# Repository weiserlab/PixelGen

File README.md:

# PixelGen: Rethinking Embedded Cameras for Mixed-Reality

## Overview
Mixed-reality headsets offer new ways to perceive our environment. They employ visible spectrum cameras to capture and display the environment on screens in front of the user's eyes. However, these cameras lead to limitations. Firstly, they capture only a partial view of the environment. They are positioned to capture whatever is in front of the user, thus creating blind spots during complete immersion and failing to detect events outside the restricted field of view. Secondly, they capture only visible light fields, ignoring other fields like acoustics and radio that are also present in the environment. Finally, these power-hungry cameras rapidly deplete the mixed-reality headset's battery. We introduce PixelGen to rethink embedded cameras for mixed-reality headsets. PixelGen proposes to decouple cameras from the mixed-reality headset and balance resolution and fidelity to minimize the power consumption. It employs low-resolution, monochrome image sensors and environmental sensors to capture the surroundings around the headset. This approach reduces the system's communication bandwidth and power consumption. A transformer-based language and image model process this information to overcome resolution trade-offs, thus generating a higher-resolution representation of the environment. 

## Demonstration
View what **`PixelGen`** can do! Here are a stream of images generated from PixelGen- 
http://bit.ly/generated_video

## Publications
1. [**ImmerCom'24**](https://dl.acm.org/doi/10.1145/3636534.3696216) - *PixelGen: Rethinking Embedded Cameras for Mixed-Reality*
   > The 2nd ACM Workshop on Mobile Immersive Computing, Networking, and Systems (**ImmerCom**) was held in conjunction with **ACM MobiCom 2024**
   ```
   @inproceedings{10.1145/3636534.3696216,
      author = {Li, Kunjun and Gulati, Manoj and Shah, Dhairya and Waskito, Steven and Chakrabarty, Shantanu and Varshney, Ambuj},
      title = {PixelGen: Rethinking Embedded Cameras for Mixed-Reality},
      year = {2024},
      isbn = {9798400704895},
      publisher = {Association for Computing Machinery},
      address = {New York, NY, USA},
      url = {https://doi.org/10.1145/3636534.3696216},
      doi = {10.1145/3636534.3696216},
      abstract = {Mixed-reality headsets offer new ways to perceive our environment. They employ visible spectrum cameras to capture and display the environment on screens in front of the user's eyes. However, these cameras lead to limitations. Firstly, they capture only a partial view of the environment. They are positioned to capture whatever is in front of the user, thus creating blind spots during complete immersion and failing to detect events outside the restricted field of view. Secondly, they capture only visible light fields, ignoring other fields like acoustics and radio that are also present in the environment. Finally, these power-hungry cameras rapidly deplete the mixed-reality headset's battery. We introduce PixelGen to rethink embedded cameras for mixed-reality headsets. PixelGen proposes to decouple cameras from the mixed-reality headset and balance resolution and fidelity to minimize the power consumption. It employs low-resolution, monochrome image sensors and environmental sensors to capture the surroundings around the headset. This approach reduces the system's communication bandwidth and power consumption. A transformer-based language and image model process this information to overcome resolution trade-offs, thus generating a higher-resolution representation of the environment. We present initial experiments that show PixelGen's viability.},
      booktitle = {Proceedings of the 30th Annual International Conference on Mobile Computing and Networking},
      pages = {2128–2135},
      numpages = {8},
      keywords = {embedded systems, networking, large language models},
      location = {Washington D.C., DC, USA},
      series = {ACM MobiCom '24}
   }
   ```
3. [**IPSN'24 Demo**](https://ieeexplore.ieee.org/document/10577362) - *PixelGen: Rethinking Embedded Camera Systems for Mixed-Reality*
   
   > PixelGen wins [*Best Demonstration Runner-Up* award](https://ipsn.acm.org/2024/awards.html) at IPSN'24.
   ```
   @INPROCEEDINGS{10577362,
      author={Li, Kunjun and Gulati, Manoj and Shah, Dhairya and Waskito, Steven and Chakrabarty, Shantanu and Varshney, Ambuj},
      booktitle={2024 23rd ACM/IEEE International Conference on Information Processing in Sensor Networks (IPSN)}, 
      title={Demo Abstract: PixelGen: Rethinking Embedded Camera Systems for Mixed-Reality}, 
      year={2024},
      volume={},
      number={},
      pages={271-272},
      keywords={Headphones;Visualization;Power demand;Magnetic sensors;Mixed reality;Virtual reality;Sensor phenomena and characterization;Embedded Camera Systems;Mixed Reality;Multimodal AI;Low-power Systems},
      doi={10.1109/IPSN61024.2024.00036}
   }
   ```

4. [**arXiv**](https://arxiv.org/abs/2402.03390) - *PixelGen: Rethinking Embedded Camera Systems*
   ```
   @misc{li2024pixelgenrethinkingembeddedcamera,
      title={PixelGen: Rethinking Embedded Camera Systems}, 
      author={Kunjun Li and Manoj Gulati and Steven Waskito and Dhairya Shah and Shantanu Chakrabarty and Ambuj Varshney},
      year={2024},
      eprint={2402.03390},
      archivePrefix={arXiv},
      primaryClass={eess.IV},
      url={https://arxiv.org/abs/2402.03390}, 
   }
   ```

## Repository Contents
This repository contains everything you need to get started with PixelGen, including scripts, hardware designs, and model compression tools.

### Pipeline
- **`fast_stable_diffusion_AUTOMATIC1111.ipynb`**: This script runs the diffusion model on collected sensor data to generate high-resolution images.
- **`ControlNet`**: This repo gives a quick guide to use controlnet with stable diffusion (either by canny edge detector or oneformer segmentation)
  
### Script
- **`capture.py`**: This script captures a low-res monochrome image using the PixelGen platform.
- **`fusion.py`**: This script captures an image and simultaneously collect sensor data.
  
### Hardware
- **`AmbiqSDK`**: Contains the driver code required to interface with the various sensors and microcontroller on the PixelGen platform.
- **`board`**: Includes the schematics of the hardware components, detailing how the sensors, microcontroller, and transceivers are interconnected. It also provides the Gerber files needed for manufacturing the custom PixelGen board.
  
### Beta
This repo contains pruning.ipynb which can compress stable diffusion 3 transformer with one-shot pruning ([SparseGPT](https://arxiv.org/abs/2301.00774)) and Tiny-SD which is a compressed stable diffusion v1.5 model with [`knowledge distillation`](https://github.com/segmind/distill-sd). Note that the work is still in progress.

## Getting Started
1. **Clone the repository**: 
   ```bash
   git clone https://github.com/weiserlab/PixelGen.git
   cd PixelGen
   ```
## Poster
This shows a high level overview of **PixelGen**.

## Contributing
We welcome contributions from the community. Please fork the repository and create a pull request with your enhancements or bug fixes.

## Team and Contact
PixelGen is developed and maintained by the following researchers from the [WEISER group](https://weiserlab.github.io/ambuj/) from the School of Computing, National University of Singapore (NUS). 
- [Kunjun Li](https://github.com/StargazerX0) 
- [Manoj Gulati](https://github.com/manojgulati)
- [Dhairya Shah](https://github.com/dhairyashah1/)
- [Steven Waskito](https://github.com/stevenantya)
- [Ambuj Varshney](https://github.com/weiserlab/)
  
Feel free to contact us at [`dhairya@u.nus.edu`](mailto:dhairya@u.nus.edu) or [`ambujv@nus.edu.sg`](mailto:ambujv@nus.edu.sg) for any questions or suggestions.

## Funding
This work was supported primarily through a grant from the NUS-NCS center, a startup grant, a MoE Tier 1 Grant, and an unrestricted gift from Google through their Research Scholar Program. All of these grants were administered through the National University of Singapore.

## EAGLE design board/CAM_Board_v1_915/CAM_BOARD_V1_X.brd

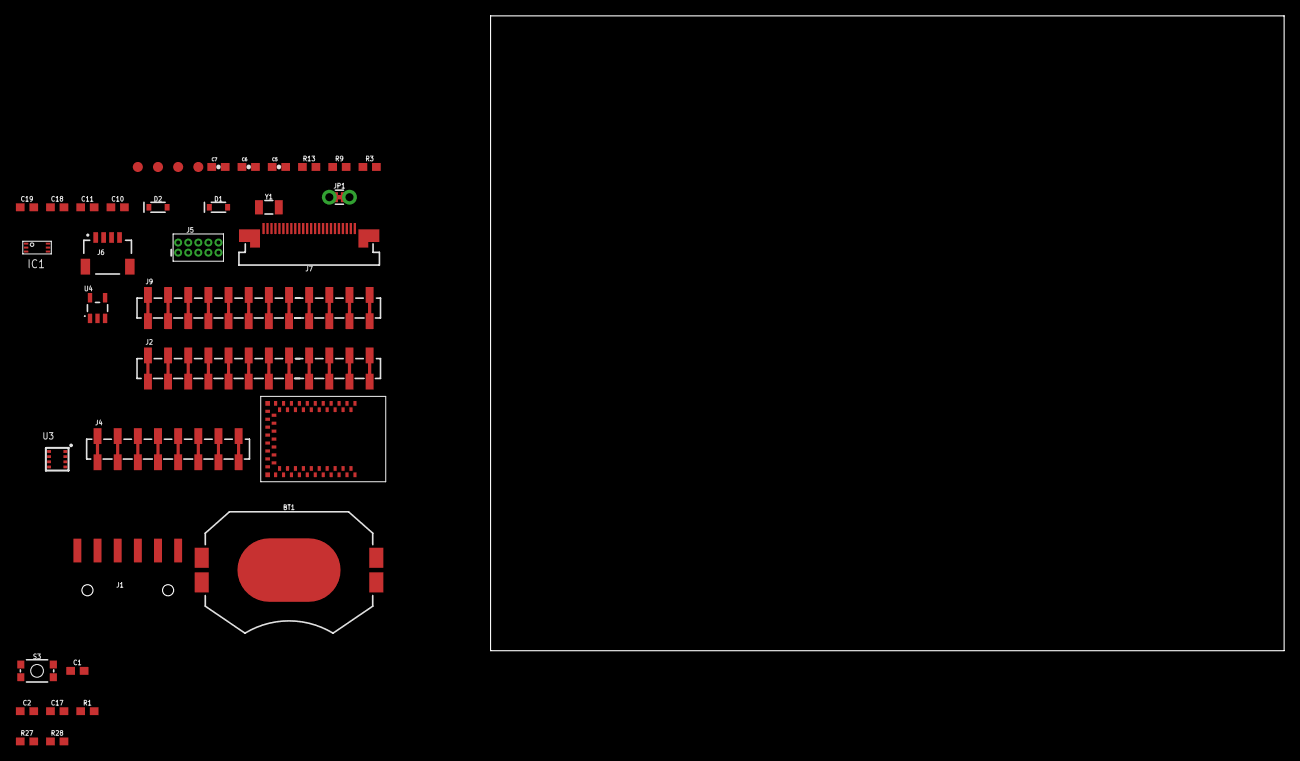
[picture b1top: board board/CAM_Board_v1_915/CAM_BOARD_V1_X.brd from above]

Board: 2 copper layers, 100.0 x 80.0 mm, 37 parts (0 on the bottom side), 63 nets, no tracks yet.

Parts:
BT1: BATTCON_20MM_4LEGS_OVERPASTE_INNER
C1, C2: 0.1uF; 0603
C5, C6, C7: 0.1uF; 0603-CAP
C10, C11: 15pF; 0603
C17: 1nF; 0603
C18, C19: 1.0uF; 0603
D1, D2: 1A/23V/620mV; SOD-323
IC1: BH1750; WSOF-6
J1: 1X06-SMD_RA_MALE
J2, J9: 1X12_SMD_COMBINED
J4: SMD; 1X08_SMD_COMBINED
J5: CORTEX_DEBUG; 2X5-PTH-1.27MM
J6: QWIIC_RIGHT_ANGLE; JST04_1MM_RA
J7: CAMERA-HIMAXBOTTOM-CONTACT; FPC-24-AMPHENOL-SFV24R-1STE1HLF
JP1: JUMPER-COMBO_2_NC_TRACE; COMBO-JUMPER_2_NC_TRACE
R1, R27: 100k; 0603
R3, R9: 1k; 0603@1
R13: 10k; 0603@1
R28: 220k; 0603
S3: RESET; TACTILE_SWITCH_SMD_4.6X2.8MM
TP1, TP2: PAD.03X.05
TP5, TP6: TEST-POINT3X5; PAD.03X.05
U2: ARTEMIS_MODULESMD; ARTEMIS_FP
U3: BME280; BME280_LGA
U4: AP2127K-1.8V; SOT23-5
Y1: 32.768kHz; CRYSTAL-SMD-3.2X1.5MM

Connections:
1.8V: C19.1, J4.7, J4.7@2, J4.8, J4.8@2, J7.10, U4.5
3.3V: J4.5, J4.5@2, J4.6, J4.6@2, J6.2
!DTR: C1.1, C2.1, J1.1, R1.2
!TGT_RST: J5.10, U2.~RST
AMBIQ_!RST: C1.2, C17.1, R27.1, S3.3, S3.4
BOOT: C2.2, R28.2
CAMERA_D0: J7.14, U2.D0
CAMERA_D1: J7.3, U2.D1
CAMERA_D2: J7.9, U2.D2
CAMERA_D3: J7.5, U2.D3
CAMERA_D4: J7.12, U2.~D4
CAMERA_D5: J7.20, U2.~D5
CAMERA_D6: J7.19, U2.~D6
CAMERA_D7: J7.13, U2.D7
CAMERA_HSYNC: J7.16, U2.D17
CAMERA_INT: J7.18, U2.D10
CAMERA_MCLK: J7.8, U2.~D18
CAMERA_PCLK: J7.17, U2.~D19
CAMERA_TRIG: J7.7, U2.D14
CAMERA_VSYNC: J7.6, U2.D15
D13: J9.5, J9.5@2, U2.~AD13
D16: J2.12, J2.12@2, U2.AD16
D23: J9.3, J9.3@2
D24: J9.1, J9.1@2, U2.~D24
D25: J9.11, J9.11@2
D26: J9.10, J9.10@2, U2.~D26
D27: J9.4, J9.4@2
D28: J9.12, J9.12@2, U2.~D28
D29: J9.8, J9.8@2, U2.~AD29
D31: J2.11, J2.11@2, U2.~AD31
D32: J9.7, J9.7@2, U2.~AD32
D33: J9.6, J9.6@2, U2.~AD33/SWO
D34: J9.9, J9.9@2, U2.AD34
D35: J9.2, J9.2@2, U2.~AD35
D36: J2.6, J2.6@2, U2.D36
D37: J2.4, J2.4@2, U2.~D37
D38: J2.5, J2.5@2, U2.D38
D39: J2.1, J2.1@2, U2.~D39
D40: J2.2, J2.2@2, U2.D40
D41: J2.10, J2.10@2, U2.D41
D42: J2.7, J2.7@2, U2.~D42
D43: J2.8, J2.8@2, U2.~D43
D44: J2.3, J2.3@2, U2.~D44
D45: J2.9, J2.9@2, U2.~D45
FTDI_VCC: D2.A, J1.4
GND: BT1.2, C5.2, C6.2, C7.2, C10.1, C11.1, C17.2, C18.2, C19.2, IC1.3, J1.6, J4.1, J4.1@2, J4.2, J4.2@2, J5.3, J5.5, J5.9, J6.1, J7.2, J7.15, R1.1, R3.1, R13.1, R28.1, S3.1, S3.2, U2.GND@1, U2.GND@22, U2.GND@38, U2.GND@39, U2.GND@47, U2.GND@59, U3.P$1, U3.P$5, U3.P$7, U4.2
unnamed: C7.1, IC1.5, R9.1
unnamed: C10.2, U2.XI, Y1.P$2
unnamed: C11.2, U2.XO, Y1.P$1
SCL: J6.4, J7.21, U2.D8
SCL2: IC1.6, U2.~D27, U3.P$4
SDA: J6.3, J7.22, U2.D9
SDA2: IC1.4, U2.~D25, U3.P$3
TGT_BOOT: R13.2, U2.BOOT
TGT_SWCLK: J5.4, TP1.P$1, U2.SWDCK
TGT_SWDIO: J5.2, TP2.P$1, U2.SWDIO
TGT_SWO: J5.6, U2.~D22
UART-RX: J1.3, TP6.P$1, U2.RXI-0
UART-TX: J1.2, TP5.P$1, U2.TXO-0
VDD: C5.1, C6.1, C18.1, IC1.1, IC1.2, J5.1, J7.4, J7.11, JP1.2, JP1.4, R3.2, R9.2, R27.2, U2.VDD@36, U2.VDD@37, U3.P$2, U3.P$6, U3.P$8, U4.1, U4.3
VIN1: D1.C, D2.C, JP1.1, JP1.3
V_BATT: BT1.1, D1.A
V_USB: J4.3, J4.3@2, J4.4, J4.4@2

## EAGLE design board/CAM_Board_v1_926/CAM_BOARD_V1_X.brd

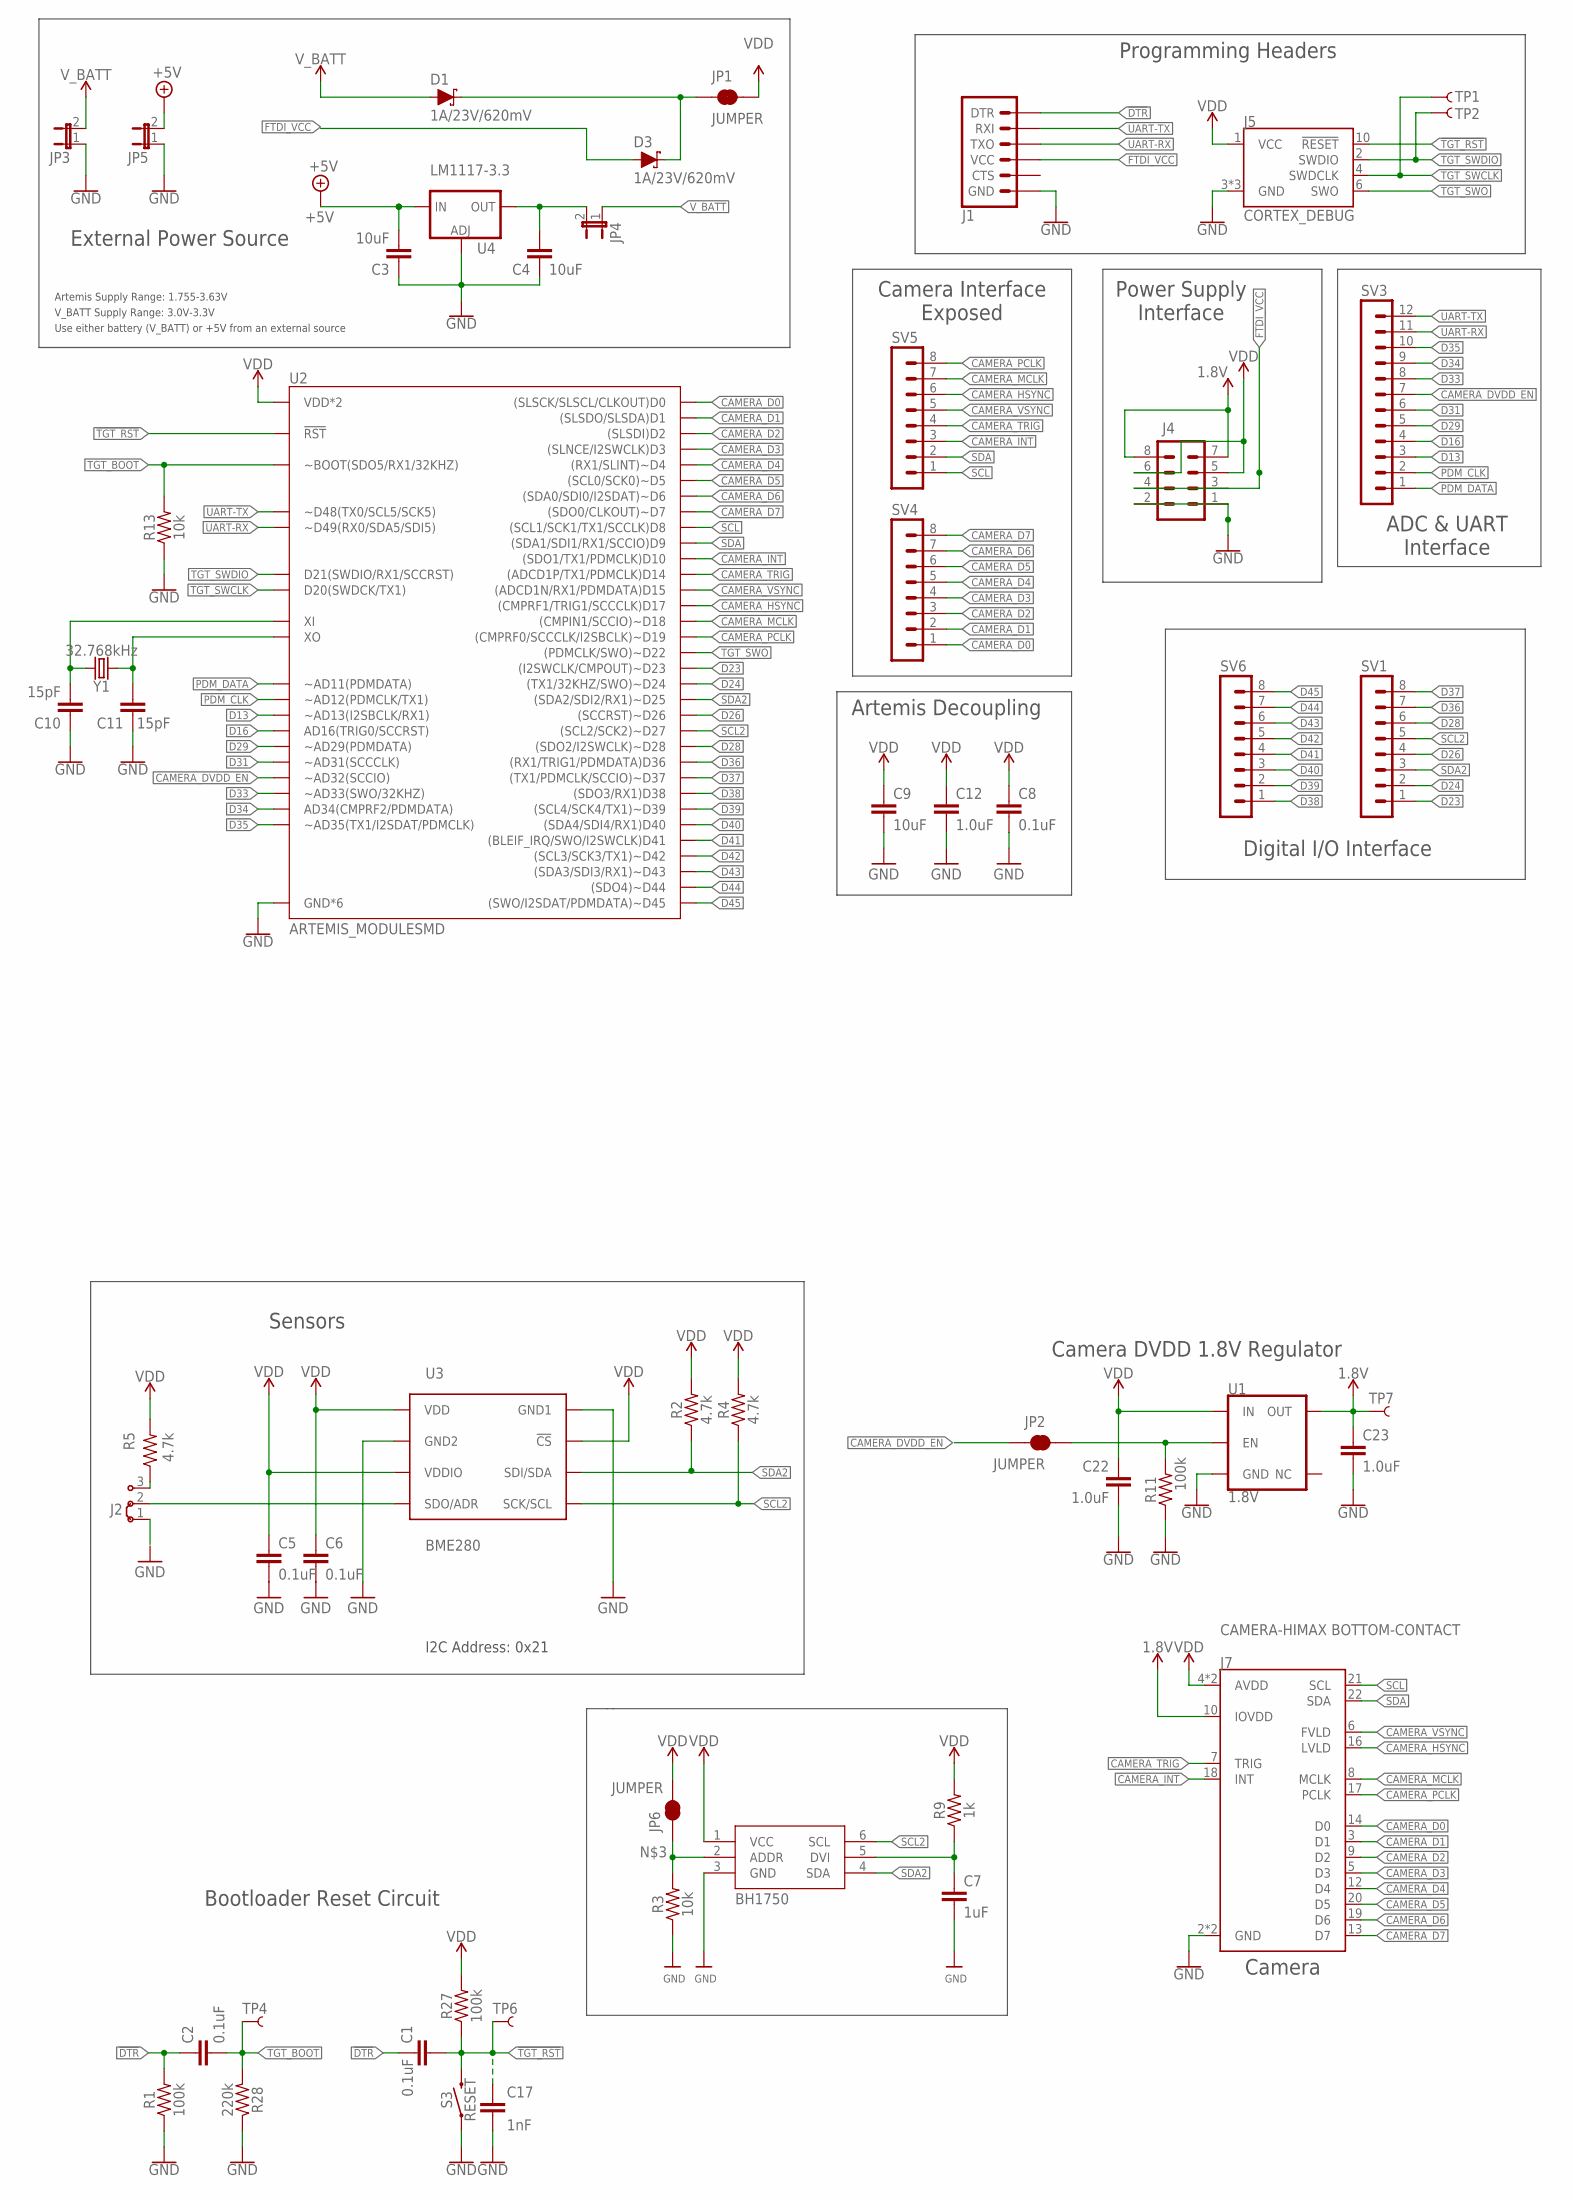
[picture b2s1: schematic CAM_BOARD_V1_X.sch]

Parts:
C1, C2: 0.1uF; 0603
C3, C4, C9: 10uF; 0603
C5, C6: 0.1uF; 0603-CAP
C7: 1uF; 0603-CAP
C8: 0.1uF; 0402-TIGHT
C10, C11: 15pF; 0603
C12, C22, C23: 1.0uF; 0402-TIGHT
C17: 1nF; 0603
D1, D3: 1A/23V/620mV; SOD-323
IC1: BH1750; WSOF-6
J1: 6_PIN_SERIAL_TARGETSMD; 1X06-SMD_RA_MALE
J2: J2X2MM; 04C
J4: MA04-2
J5: CORTEX_DEBUG; 2X5-PTH-1.27MM
J7: CAMERA-HIMAX BOTTOM-CONTACT; FPC-24-AMPHENOL-SFV24R-1STE1HLF
JP1, JP2, JP6: JUMPER; COMBO-JUMPER_2_NC_TRACE
JP3, JP4, JP5: JP1E; JP1
R1, R27: 100k; 0603
R2, R4, R5: 4.7k; 0603@1
R3, R13: 10k; 0603@1
R9: 1k; 0603@1
R11: 100k; 0402-TIGHT
R28: 220k; 0603
S3: RESET; TACTILE_SWITCH_SMD_4.6X2.8MM
SV1, SV4, SV5, SV6: MA08-1
SV3: MA12-1
TP1, TP2, TP4, TP6, TP7: TEST-POINT3X5; PAD.03X.05
U1: 1.8V; SOT23-5
U2: ARTEMIS_MODULESMD; ARTEMIS_FP
U3: BME280; BME280_LGA
U4: LM1117-3.3; SOT223
Y1: 32.768kHz; CRYSTAL-SMD-3.2X1.5MM

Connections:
1.8V: C23.1, J4.7, J4.8, J7.10 (IOVDD), TP7.P$1, U1.5 (OUT)
!DTR: C1.1, C2.1, J1.1 (DTR), R1.2
!TGT_RST: C1.2, C17.1, J5.10 (!RESET), R27.1, S3.3 (2), S3.4 (2), TP6.P$1, U2.~RST (!RST)
+5V: C3.2, JP5.2, U4.3 (IN)
CAMERA_D0: J7.14 (D0), SV4.1, U2.D0 ((SLSCK/SLSCL/CLKOUT)D0)
CAMERA_D1: J7.3 (D1), SV4.2, U2.D1 ((SLSDO/SLSDA)D1)
CAMERA_D2: J7.9 (D2), SV4.3, U2.D2 ((SLSDI)D2)
CAMERA_D3: J7.5 (D3), SV4.4, U2.D3 ((SLNCE/I2SWCLK)D3)
CAMERA_D4: J7.12 (D4), SV4.5, U2.~D4 ((RX1/SLINT)~D4)
CAMERA_D5: J7.20 (D5), SV4.6, U2.~D5 ((SCL0/SCK0)~D5)
CAMERA_D6: J7.19 (D6), SV4.7, U2.~D6 ((SDA0/SDI0/I2SDAT)~D6)
CAMERA_D7: J7.13 (D7), SV4.8, U2.D7 ((SDO0/CLKOUT)~D7)
CAMERA_DVDD_EN: JP2.1, JP2.3 (1), SV3.7, U2.~AD32 (~AD32(SCCIO))
CAMERA_HSYNC: J7.16 (LVLD), SV5.6, U2.D17 ((CMPRF1/TRIG1/SCCCLK)D17)
CAMERA_INT: J7.18 (INT), SV5.3, U2.D10 ((SDO1/TX1/PDMCLK)D10)
CAMERA_MCLK: J7.8 (MCLK), SV5.7, U2.~D18 ((CMPIN1/SCCIO)~D18)
CAMERA_PCLK: J7.17 (PCLK), SV5.8, U2.~D19 ((CMPRF0/SCCCLK/I2SBCLK)~D19)
CAMERA_TRIG: J7.7 (TRIG), SV5.4, U2.D14 ((ADCD1P/TX1/PDMCLK)D14)
CAMERA_VSYNC: J7.6 (FVLD), SV5.5, U2.D15 ((ADCD1N/RX1/PDMDATA)D15)
D13: SV3.3, U2.~AD13 (~AD13(I2SBCLK/RX1))
D16: SV3.4, U2.AD16 (AD16(TRIG0/SCCRST))
D23: SV1.1, U2.~D23 ((I2SWCLK/CMPOUT)~D23)
D24: SV1.2, U2.~D24 ((TX1/32KHZ/SWO)~D24)
D26: SV1.4, U2.~D26 ((SCCRST)~D26)
D28: SV1.6, U2.~D28 ((SDO2/I2SWCLK)~D28)
D29: SV3.5, U2.~AD29 (~AD29(PDMDATA))
D31: SV3.6, U2.~AD31 (~AD31(SCCCLK))
D33: SV3.8, U2.~AD33/SWO (~AD33(SWO/32KHZ))
D34: SV3.9, U2.AD34 (AD34(CMPRF2/PDMDATA))
D35: SV3.10, U2.~AD35 (~AD35(TX1/I2SDAT/PDMCLK))
D36: SV1.7, U2.D36 ((RX1/TRIG1/PDMDATA)D36)
D37: SV1.8, U2.~D37 ((TX1/PDMCLK/SCCIO)~D37)
D38: SV6.1, U2.D38 ((SDO3/RX1)D38)
D39: SV6.2, U2.~D39 ((SCL4/SCK4/TX1)~D39)
D40: SV6.3, U2.D40 ((SDA4/SDI4/RX1)D40)
D41: SV6.4, U2.D41 ((BLEIF_IRQ/SWO/I2SWCLK)D41)
D42: SV6.5, U2.~D42 ((SCL3/SCK3/TX1)~D42)
D43: SV6.6, U2.~D43 ((SDA3/SDI3/RX1)~D43)
D44: SV6.7, U2.~D44 ((SDO4)~D44)
D45: SV6.8, U2.~D45 ((SWO/I2SDAT/PDMDATA)~D45)
FTDI_VCC: D3.A, J1.4 (VCC), J4.3, J4.4
GND: C3.1, C4.1, C5.2, C6.2, C7.2, C8.1, C9.2, C10.1, C11.1, C12.2, C17.2, C22.2, C23.2, IC1.3 (GND), J1.6 (GND), J4.1, J4.2, J5.3 (GND), J5.5 (GND), J5.9 (GND), J7.2 (GND), J7.15 (GND), JP3.1, JP5.1, R1.1, R3.1, R11.1, R13.1, R28.1, S3.1, S3.2 (1), U1.2 (GND), U2.GND@1 (GND*6), U2.GND@22 (GND*6), U2.GND@38 (GND*6), U2.GND@39 (GND*6), U2.GND@47 (GND*6), U2.GND@59 (GND*6), U3.P$1 (GND1), U3.P$7 (GND2), U4.1 (ADJ)
unnamed: JP2.2, JP2.4 (2), R11.2, U1.3 (EN)
unnamed: C7.1, IC1.5 (DVI), R9.1
unnamed: IC1.2 (ADDR), JP6.1, JP6.3 (1), R3.2
unnamed: C4.2, JP4.2, U4.2 (OUT), U4.4 (OUT)
unnamed: J2.3, R5.1
unnamed: J2.2, U3.P$5 (SDO/ADR)
unnamed: C10.2, U2.XI, Y1.P$2 (2)
unnamed: C11.2, U2.XO, Y1.P$1 (1)
PDM_CLK: SV3.2, U2.~AD12 (~AD12(PDMCLK/TX1))
PDM_DATA: SV3.1, U2.~AD11 (~AD11(PDMDATA))
SCL: J7.21 (SCL), SV5.1, U2.D8 ((SCL1/SCK1/TX1/SCCLK)D8)
SCL1: J2.1
SCL2: IC1.6 (SCL), R4.1, SV1.5, U2.~D27 ((SCL2/SCK2)~D27), U3.P$4 (SCK/SCL)
SDA: J7.22 (SDA), SV5.2, U2.D9 ((SDA1/SDI1/RX1/SCCIO)D9)
SDA2: IC1.4 (SDA), R2.1, SV1.3, U2.~D25 ((SDA2/SDI2/RX1)~D25), U3.P$3 (SDI/SDA)
TGT_BOOT: C2.2, R13.2, R28.2, TP4.P$1, U2.BOOT (~BOOT(SDO5/RX1/32KHZ))
TGT_SWCLK: J5.4 (SWDCLK), TP1.P$1, U2.SWDCK (D20(SWDCK/TX1))
TGT_SWDIO: J5.2 (SWDIO), TP2.P$1, U2.SWDIO (D21(SWDIO/RX1/SCCRST))
TGT_SWO: J5.6 (SWO), U2.~D22 ((PDMCLK/SWO)~D22)
UART-RX: J1.3 (TXO), SV3.11, U2.RXI-0 (~D49(RX0/SDA5/SDI5))
UART-TX: J1.2 (RXI), SV3.12, U2.TXO-0 (~D48(TX0/SCL5/SCK5))
VDD: C5.1, C6.1, C8.2, C9.1, C12.1, C22.1, IC1.1 (VCC), J4.5, J4.6, J5.1 (VCC), J7.4 (AVDD), J7.11 (AVDD), JP1.2, JP1.4 (2), JP6.2, JP6.4 (2), R2.2, R4.2, R5.2, R9.2, R27.2, U1.1 (IN), U2.VDD@36 (VDD*2), U2.VDD@37 (VDD*2), U3.P$2 (!CS), U3.P$6 (VDDIO), U3.P$8 (VDD)
VIN1: D1.C, D3.C, JP1.1, JP1.3 (1)
V_BATT: D1.A, JP3.2, JP4.1

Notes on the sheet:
Programming Headers
I2C Address: 0x21
Camera
Sensors
Artemis Supply Range: 1.755-3.63V
External Power Source
Bootloader Reset Circuit
Camera DVDD 1.8V Regulator
Artemis Decoupling
V_BATT Supply Range: 3.0V-3.3V
Use either battery (V_BATT) or +5V from an external source
Camera Interface Exposed
ADC & UART Interface
Power Supply Interface
Digital I/O Interface

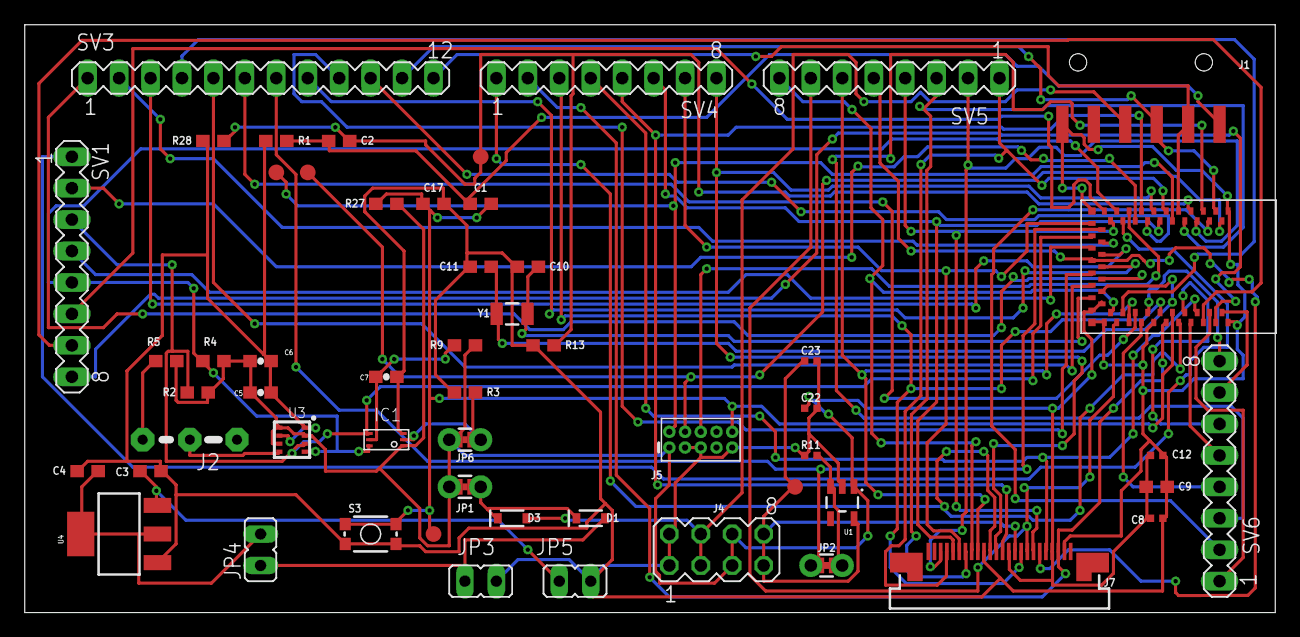
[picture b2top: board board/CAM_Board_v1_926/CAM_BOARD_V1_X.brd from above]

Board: 2 copper layers, 101.0 x 47.5 mm, 55 parts (0 on the bottom side), 65 nets.

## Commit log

2024-06-06 Code base for SDK
2024-06-06 Scripts for Camera and sensors
2024-06-06 Audio code
2024-06-06 Audio code in Arduino
2024-06-06 Stable Diffusion Colab
2024-06-06 Previous board schematic
2024-06-06 board
2024-07-31 Overview
2024-07-31 Script
2024-07-31 Model Pruning
2024-07-31 Pipeline
2024-08-01 Cloud drive link
2024-08-01 Fix error
2024-09-17 Create LICENSE
2024-09-18 Poster
2024-09-18 PixelGen Video
2024-09-18 Private Link
2024-09-18 PixelGen Pipeline
2024-09-18 Remove Redundant Code
2024-09-30 PixelGen pipeline documentation
2024-09-30 add poster
2024-09-30 correct link
2024-09-30 controlnet
2024-09-30 canny
2024-09-30 remove redundatn
2024-09-30 banner
2024-09-30 add award
2024-09-30 change repo layout
2024-09-30 add link for pruning
2024-09-30 add kd
2024-09-30 add script
2024-11-12 Updated README.md with team and publications
2024-11-15 Added PixelGen demo image png
2024-11-15 Reordered poster in README.md

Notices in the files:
parts and their libraries:
SparkFun-Batteries: Licensing: Creative Commons ShareAlike 4.0 International - https://creativecommons.org/licenses/by-sa/4.0
microbuilder: This work is placed in the public domain, and may be freely used for commercial and non-commercial work with the following conditions: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
